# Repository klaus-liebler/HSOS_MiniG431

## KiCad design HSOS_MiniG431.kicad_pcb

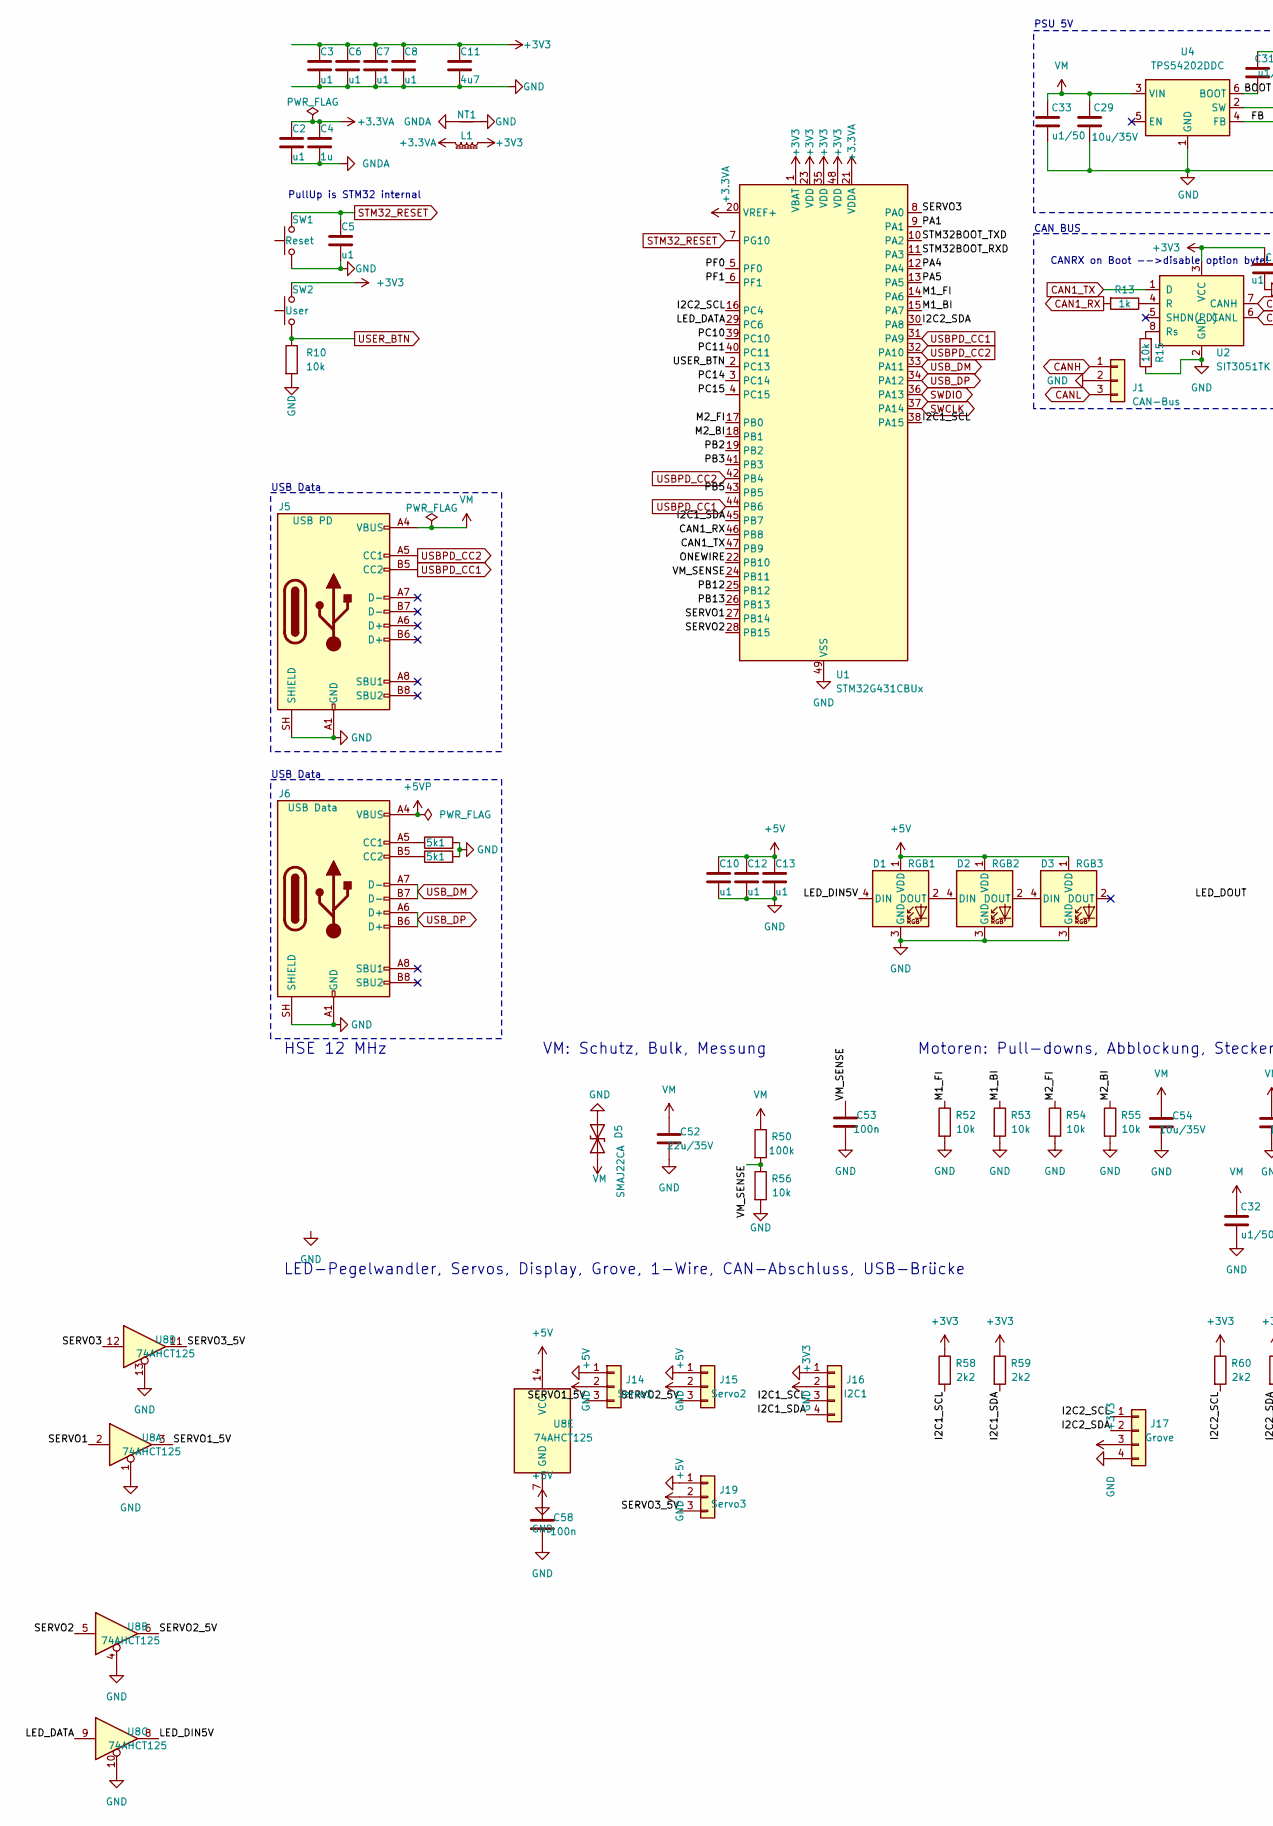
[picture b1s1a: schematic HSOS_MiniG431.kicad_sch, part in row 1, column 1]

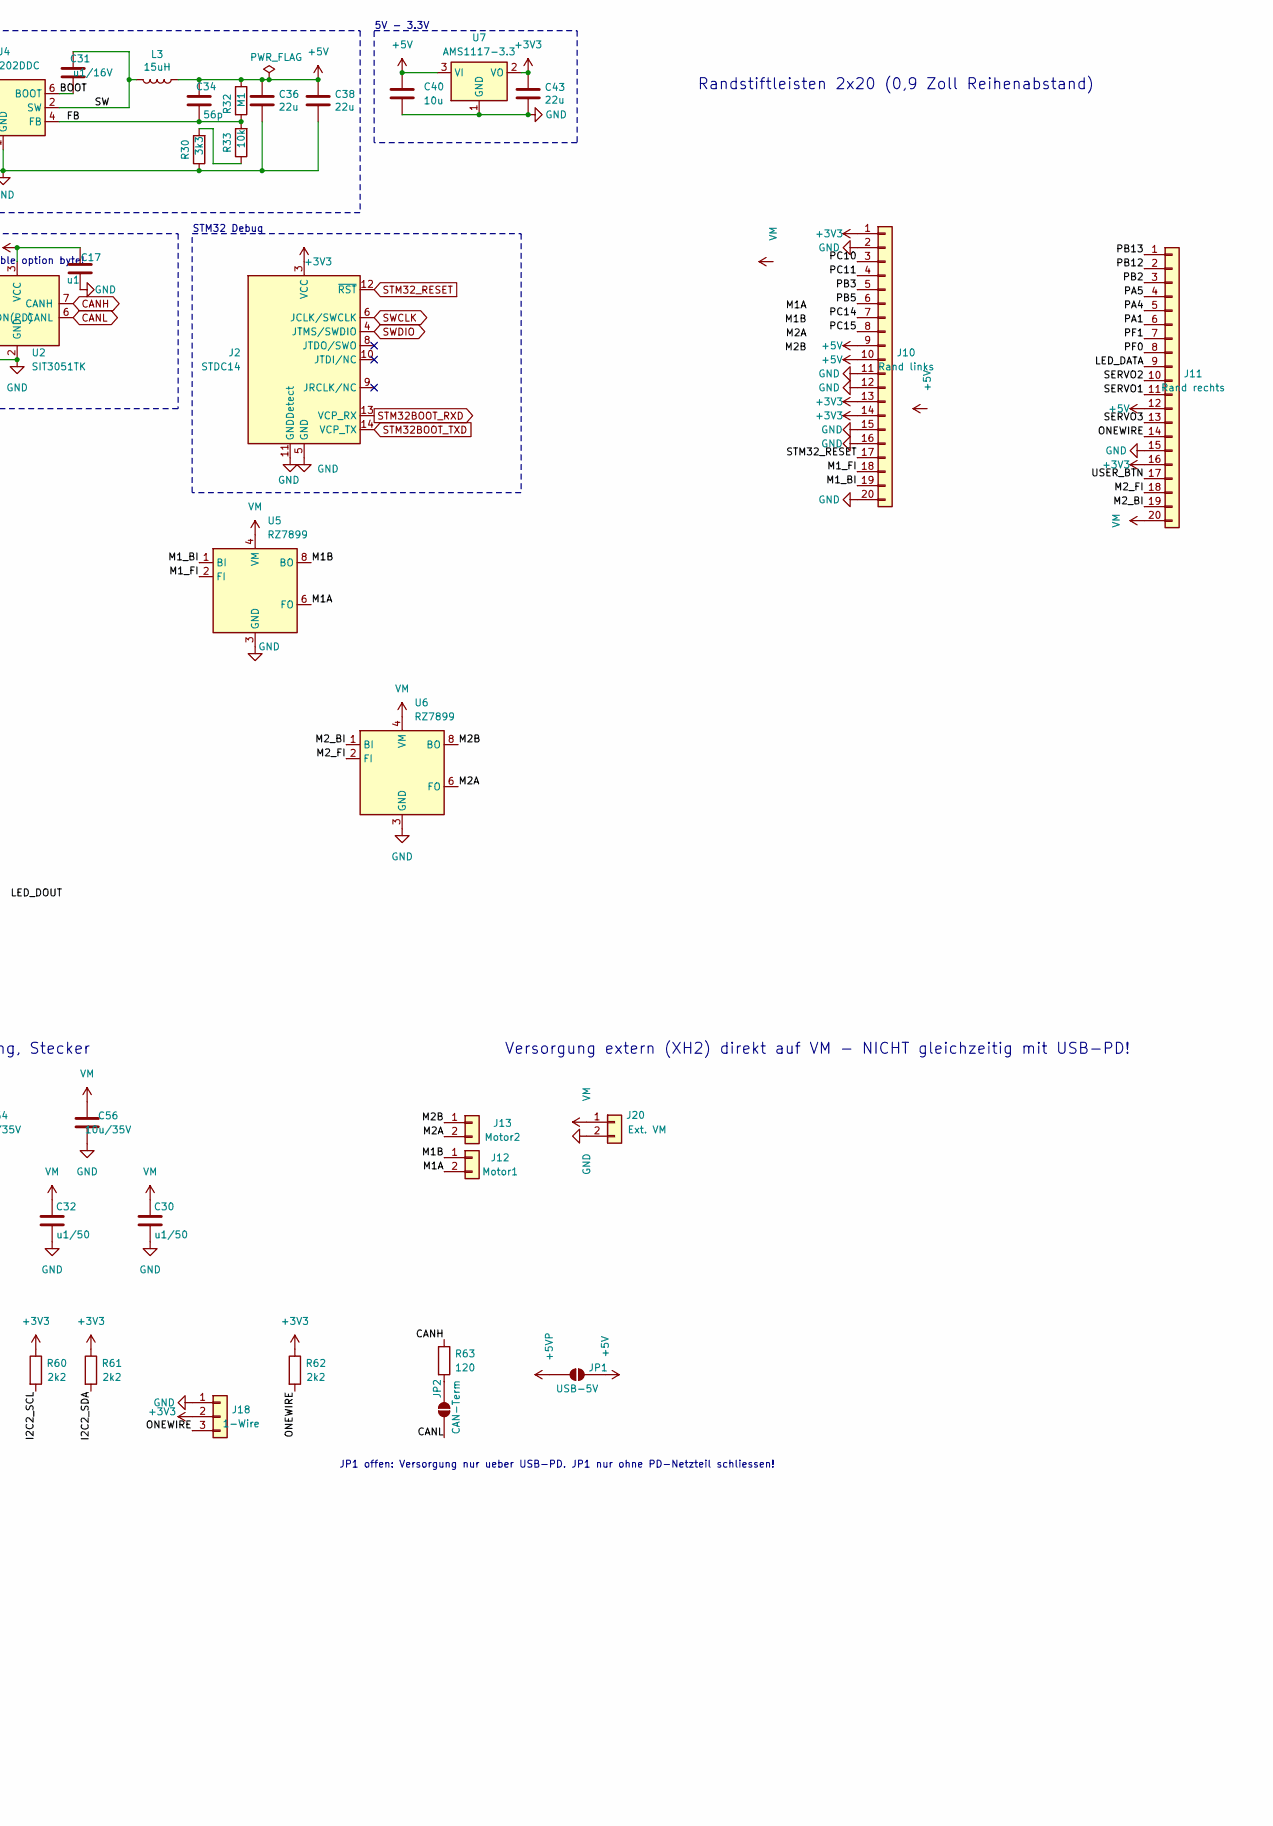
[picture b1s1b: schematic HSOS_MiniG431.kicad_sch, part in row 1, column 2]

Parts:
C2, C3, C5, C6, C7, C8, C10, C12, C13: u1; C_0402_1005Metric; LCSC C1525
C4: 1u; C_0402_1005Metric; LCSC C52923
C11: 4u7; C_0402_1005Metric; LCSC C307423
C17: u1; C_0402_1005Metric; MPN GRM033R61A104KE15D; LCSC C1525
C29: 10u/35V; C_0805_2012Metric; MPN CGA0805X5R106K350MT; LCSC C6119889
C30, C32, C33: u1/50; C_0603_1608Metric; LCSC C14663
C31: u1/16V; C_0402_1005Metric; MPN CC0603KRX7R9BB104; LCSC C1525
C34: 56p; C_0402_1005Metric; MPN CC0402JRNPO9BN560; LCSC C107007
C36, C38, C43: 22u; C_0805_2012Metric; MPN CL10A226MP8NUNE; LCSC C45783
C40: 10u; C_0805_2012Metric; LCSC C6119889
C52: 22u/35V; C_0805_2012Metric; LCSC C6119901
C53, C58: 100n; C_0402_1005Metric; LCSC C1525
C54, C56: 10u/35V; C_0805_2012Metric; LCSC C6119889
D1: RGB1; SK6812MINI-E_REV; LCSC C5149201
D2: RGB2; SK6812MINI-E_REV; LCSC C5149201
D3: RGB3; SK6812MINI-E_REV; LCSC C5149201
D5: SMAJ22CA; D_SMA; LCSC C353463
J1: CAN-Bus; JST_XH_B3B-XH-A_1x03_P2.50mm_Vertical_smaller
J2: STDC14; PinHeader_2x07_P1.27mm_Vertical; LCSC C54930112
J5: USB PD; USB_C_Receptacle_HRO_TYPE-C-31-M-12_smaller; MPN TYPE-C-31-M-12; LCSC C165948
J6: USB Data; USB_C_Receptacle_HRO_TYPE-C-31-M-12_smaller; MPN TYPE-C-31-M-12; LCSC C165948
J10: Rand links; PinHeader_1x20_P2.54mm_Vertical
J11: Rand rechts; PinHeader_1x20_P2.54mm_Vertical
J12: Motor1; JST_XH_B2B-XH-A_1x02_P2.50mm_Vertical
J13: Motor2; JST_XH_B2B-XH-A_1x02_P2.50mm_Vertical
J14: Servo1; PinHeader_1x03_P2.54mm_Vertical
J15: Servo2; PinHeader_1x03_P2.54mm_Vertical
J16: I2C1; PinSocket_1x04_P2.54mm_Vertical
J17: Grove; JST_PH_B4B-PH-K_1x04_P2.00mm_Vertical; LCSC C22388606
J18: 1-Wire; PinHeader_1x03_P2.54mm_Vertical
J19: Servo3; PinHeader_1x03_P2.54mm_Vertical
J20: Ext. VM; JST_XH_B2B-XH-A_1x02_P2.50mm_Vertical
JP1: USB-5V; SolderJumper-2_P1.3mm_Open_RoundedPad1.0x1.5mm
JP2: CAN-Term; SolderJumper-2_P1.3mm_Open_RoundedPad1.0x1.5mm
L1: 220R@100M; L_0603_1608Metric; LCSC C80165
L3: 15uH; L_Abracon_ASPI-0630LR; MPN FXL0630-100-M; LCSC C177243
NT1: NetTie_2; NetTie-2_SMD_Pad0.5mm
R10, R52, R53, R54, R55, R56: 10k; R_0402_1005Metric; LCSC C25744
R13: 1k; R_0402_1005Metric; MPN 0402WGF1001TCE; LCSC C11702
R15, R33: 10k; R_0402_1005Metric; MPN 0201WMF1002TEE; LCSC C25744
R30: 3k3; R_0402_1005Metric; MPN 0402WGF3301TCE; LCSC C25890
R32: M1; R_0402_1005Metric; MPN 0201WMF1003TEE; LCSC C25741
R45, R46: 5k1; R_0402_1005Metric; LCSC C25905
R50: 100k; R_0402_1005Metric; LCSC C25741
R58, R59, R60, R61, R62: 2k2; R_0402_1005Metric; LCSC C25879
R63: 120; R_0603_1608Metric; LCSC C22787
SW1: Reset; SW_Push_1P1T_NO_6x6mm_H6.5mm_Reverse; LCSC C541960
SW2: User; SW_Push_1P1T_NO_6x6mm_H6.5mm_Reverse; LCSC C541960
U1: STM32G431CBUx; QFN-48-1EP_7x7mm_P0.5mm_EP5.6x5.6mm; LCSC C529356
U2: SIT3051TK; DFN-8-1EP_3x3mm_P0.65mm_EP1.55x2.4mm; LCSC C601078
U4: TPS54202DDC; SOT-23-6; MPN TPS54202DDCR; LCSC C191884
U5, U6: RZ7899; SOP-8_3.76x4.96mm_P1.27mm; LCSC C22462553
U7: AMS1117-3.3; SOT-223-3_TabPin2; LCSC C6186
U8: 74AHCT125; TSSOP-14_4.4x5mm_P0.65mm; LCSC C176917

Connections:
+3.3VA: C2.1, C4.1, L1.2, U1.20 (VREF+), U1.21 (VDDA)
+3V3: C3.1, C6.1, C7.1, C8.1, C11.1, C17.1, C43.1, J2.3 (VCC), J10.1, J10.13, J10.14, J11.16, J16.2, J17.3, J18.2, L1.1, R58.1, R59.1, R60.1, R61.1, R62.1, SW2.2, U1.1 (VBAT), U1.23 (VDD), U1.35 (VDD), U1.48 (VDD), U2.3 (VCC), U7.2 (VO)
+5V: C10.1, C12.1, C13.1, C34.2, C36.1, C38.1, C40.1, C58.1, D1.1 (VDD), D2.1 (VDD), D3.1 (VDD), J10.9, J10.10, J11.12, J14.2, J15.2, J19.2, JP1.2 (B), L3.1, R32.1, U7.3 (VI), U8.14 (VCC)
+5VP: J6.A4 (VBUS), J6.A9 (VBUS), J6.B4 (VBUS), J6.B9 (VBUS), JP1.1 (A)
/BOOT: C31.1, U4.6 (BOOT)
/FB: C34.1, R32.2, R33.2, U4.4 (FB)
/I2C1_SCL: J16.3, R58.2, U1.38 (PA15)
/I2C1_SDA: J16.4, R59.2, U1.45 (PB7)
/I2C2_SCL: J17.1, R60.2, U1.16 (PC4)
/I2C2_SDA: J17.2, R61.2, U1.30 (PA8)
/LED_DATA: J11.9, U1.29 (PC6), U8.9
/LED_DIN5V: D1.4 (DIN), U8.8
/M1A: J12.2, U5.5 (FO), U5.6 (FO)
/M1B: J12.1, U5.7 (BO), U5.8 (BO)
/M1_BI: J10.19, R53.1, U1.15 (PA7), U5.1 (BI)
/M1_FI: J10.18, R52.1, U1.14 (PA6), U5.2 (FI)
/M2A: J13.2, U6.5 (FO), U6.6 (FO)
/M2B: J13.1, U6.7 (BO), U6.8 (BO)
/M2_BI: J11.19, R55.1, U1.18 (PB1), U6.1 (BI)
/M2_FI: J11.18, R54.1, U1.17 (PB0), U6.2 (FI)
/ONEWIRE: J11.14, J18.3, R62.2, U1.22 (PB10)
/PA1: J11.6, U1.9 (PA1)
/PA4: J11.5, U1.12 (PA4)
/PA5: J11.4, U1.13 (PA5)
/PB2: J11.3, U1.19 (PB2)
/PB3: J10.5, U1.41 (PB3)
/PB5: J10.6, U1.43 (PB5)
/PB12: J11.2, U1.25 (PB12)
/PB13: J11.1, U1.26 (PB13)
/PC10: J10.3, U1.39 (PC10)
/PC11: J10.4, U1.40 (PC11)
/PC14: J10.7, U1.3 (PC14)
/PC15: J10.8, U1.4 (PC15)
/PF0: J11.8, U1.5 (PF0)
/PF1: J11.7, U1.6 (PF1)
/SERVO1: J11.11, U1.27 (PB14), U8.2
/SERVO1_5V: J14.3, U8.3
/SERVO2: J11.10, U1.28 (PB15), U8.5
/SERVO2_5V: J15.3, U8.6
/SERVO3: J11.13, U1.8 (PA0), U8.12
/SERVO3_5V: J19.3, U8.11
/SW: C31.2, L3.2, U4.2 (SW)
/VM_SENSE: C53.1, R50.2, R56.1, U1.24 (PB11); also elsewhere on the board
CAN1_RX: R13.2, U1.46 (PB8)
CAN1_TX: U1.47 (PB9), U2.1 (D)
CANH: J1.1, R63.1, U2.7 (CANH)
CANL: J1.3, JP2.1 (A), U2.6 (CANL)
GND: C3.2, C5.2, C6.2, C7.2, C8.2, C10.2, C11.2, C12.2, C13.2, C17.2, C29.1, C30.1, C32.1, C33.1, C36.2, C38.2, C40.2, C43.2, C52.2, C53.2, C54.2, C56.2, C58.2, D1.3 (GND), D2.3 (GND), D3.3 (GND), D5.2 (A2), J1.2, J2.5 (GND), J2.7 (GND), J2.11 (GNDDetect), J5.A1 (GND), J5.A12 (GND), J5.B1 (GND), J5.B12 (GND), J5.SH (SHIELD), J6.A1 (GND), J6.A12 (GND), J6.B1 (GND), J6.B12 (GND), J6.SH (SHIELD), J10.2, J10.11, J10.12, J10.15, J10.16, J10.20, J11.15, J14.1, J15.1, J16.1, J17.4, J18.1, J19.1, J20.2, NT1.2, R10.2, R15.1, R30.1, R45.2, R46.2, R52.2, R53.2, R54.2, R55.2, R56.2, SW1.1, U1.49 (VSS), U2.2 (GND), U2.9 (PAD), U4.1 (GND), U5.3 (GND), U6.3 (GND), U7.1 (GND), U8.1, U8.4, U8.7 (GND), U8.10, U8.13; also elsewhere on the board
GNDA: C2.2, C4.2, NT1.1
unnamed: D1.2 (DOUT), D2.4 (DIN)
unnamed: D2.2 (DOUT), D3.4 (DIN)
unnamed: J6.A5 (CC1), R45.1
unnamed: J6.B5 (CC2), R46.1
unnamed: JP2.2 (B), R63.2
unnamed: R30.2, R33.1
unnamed: R13.1, U2.4 (R)
unnamed: R15.2, U2.8 (Rs)
STM32BOOT_RXD: J2.13 (VCP_RX), U1.11 (PA3)
STM32BOOT_TXD: J2.14 (VCP_TX), U1.10 (PA2)
STM32_RESET: C5.1, J2.12 (~RST), J10.17, SW1.2, U1.7 (PG10)
SWCLK: J2.6 (JCLK/SWCLK), U1.37 (PA14)
SWDIO: J2.4 (JTMS/SWDIO), U1.36 (PA13)
USBPD_CC1: J5.B5 (CC2), U1.31 (PA9), U1.44 (PB6)
USBPD_CC2: J5.A5 (CC1), U1.32 (PA10), U1.42 (PB4)
USB_DM: J6.A7 (D-), J6.B7 (D-), U1.33 (PA11)
USB_DP: J6.A6 (D+), J6.B6 (D+), U1.34 (PA12)
USER_BTN: J11.17, R10.1, SW2.1, U1.2 (PC13)
VM: C29.2, C30.2, C32.2, C33.2, C52.1, C54.1, C56.1, D5.1 (A1), J5.A4 (VBUS), J5.A9 (VBUS), J5.B4 (VBUS), J5.B9 (VBUS), J11.20, J20.1, R50.1, U4.3 (VIN), U5.4 (VM), U6.4 (VM)

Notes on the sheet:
JP1 offen: Versorgung nur ueber USB-PD. JP1 nur ohne PD-Netzteil schliessen!
PullUp is STM32 internal
LED-Pegelwandler, Servos, Display, Grove, 1-Wire, CAN-Abschluss, USB-Brücke
USB Data
Motoren: Pull-downs, Abblockung, Stecker
CANRX on Boot -->disable option byte!
CAN BUS
5V - 3.3V
STM32 Debug
Versorgung extern (XH2) direkt auf VM - NICHT gleichzeitig mit USB-PD!
HSE 12 MHz
Randstiftleisten 2x20 (0,9 Zoll Reihenabstand)
VM: Schutz, Bulk, Messung
PSU 5V

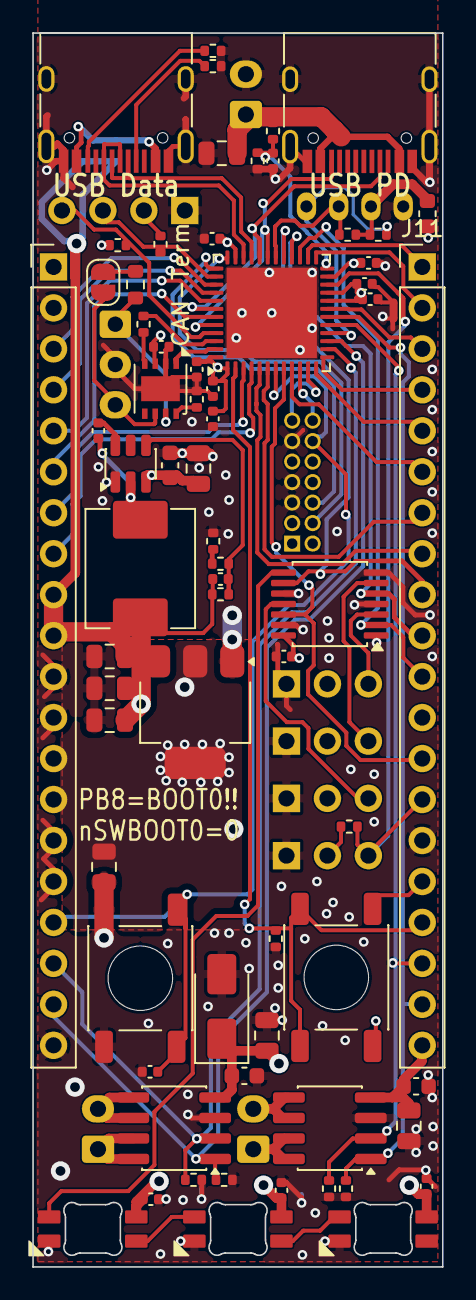
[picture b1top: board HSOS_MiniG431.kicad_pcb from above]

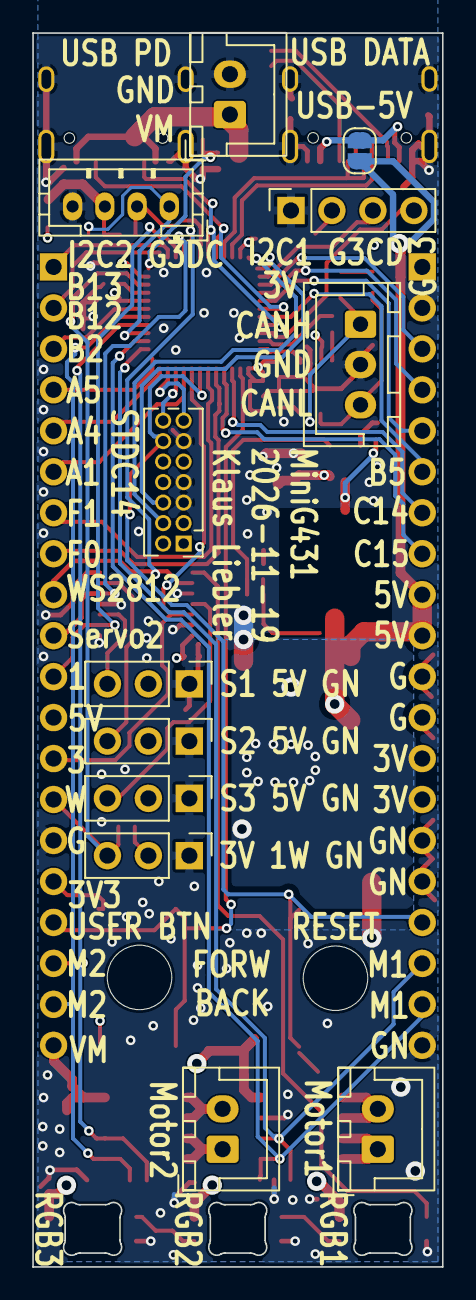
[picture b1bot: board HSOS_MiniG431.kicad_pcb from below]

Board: 4 copper layers, 25.4 x 76.5 mm, 80 parts (12 on the bottom side), 68 nets.

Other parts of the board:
R51: 15k; R_0402_1005Metric

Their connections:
/VM_SENSE: R51.1; also elsewhere on the board
GND: R51.2; also elsewhere on the board
